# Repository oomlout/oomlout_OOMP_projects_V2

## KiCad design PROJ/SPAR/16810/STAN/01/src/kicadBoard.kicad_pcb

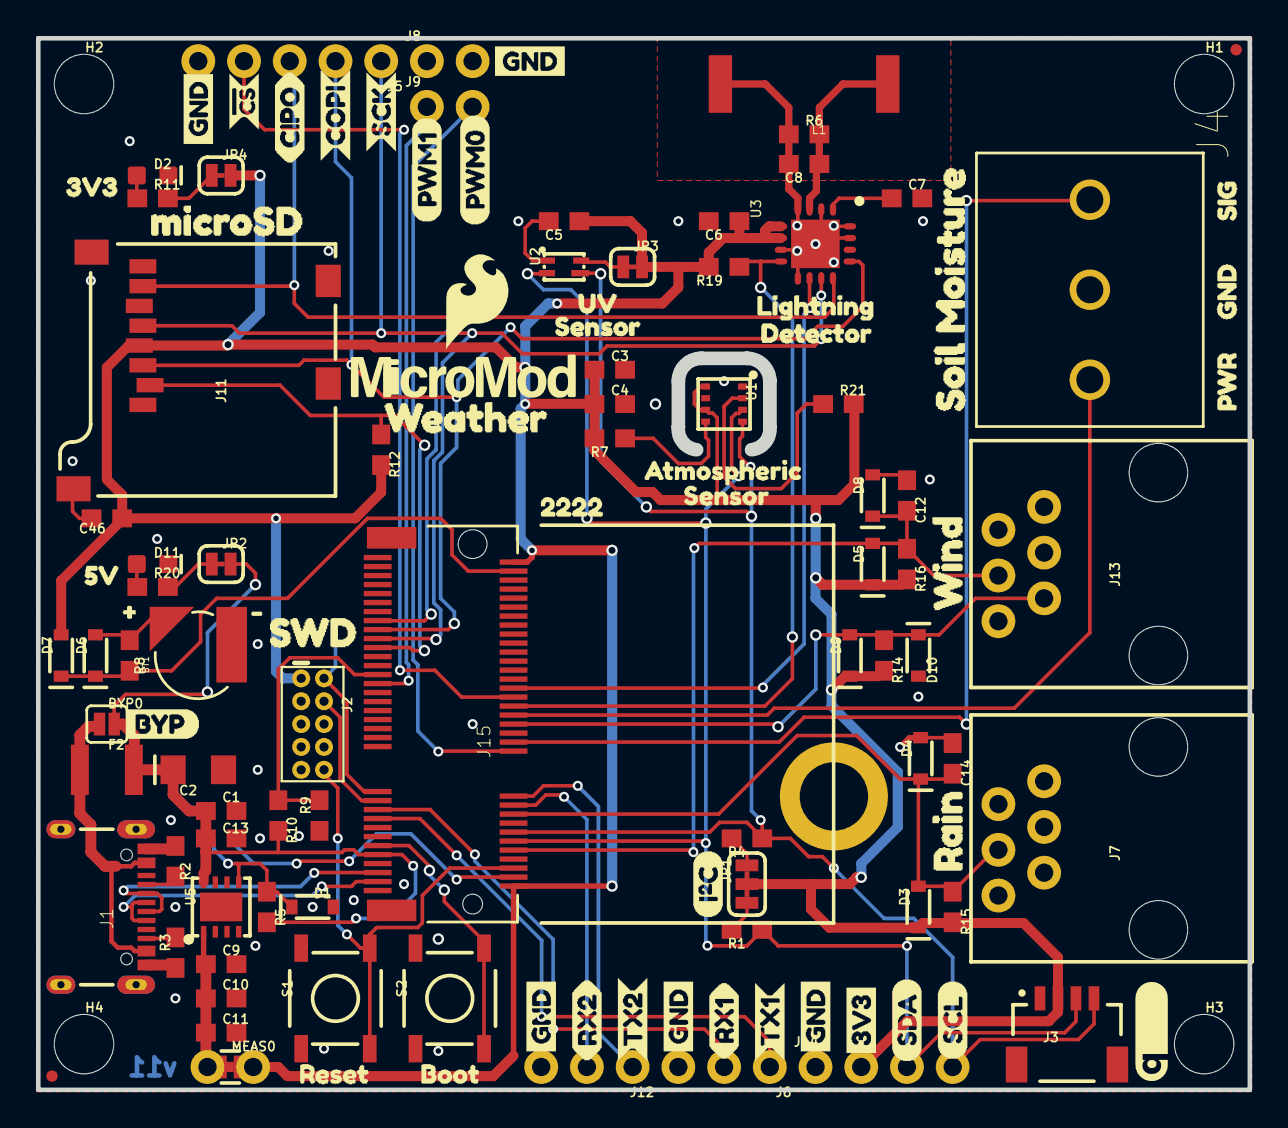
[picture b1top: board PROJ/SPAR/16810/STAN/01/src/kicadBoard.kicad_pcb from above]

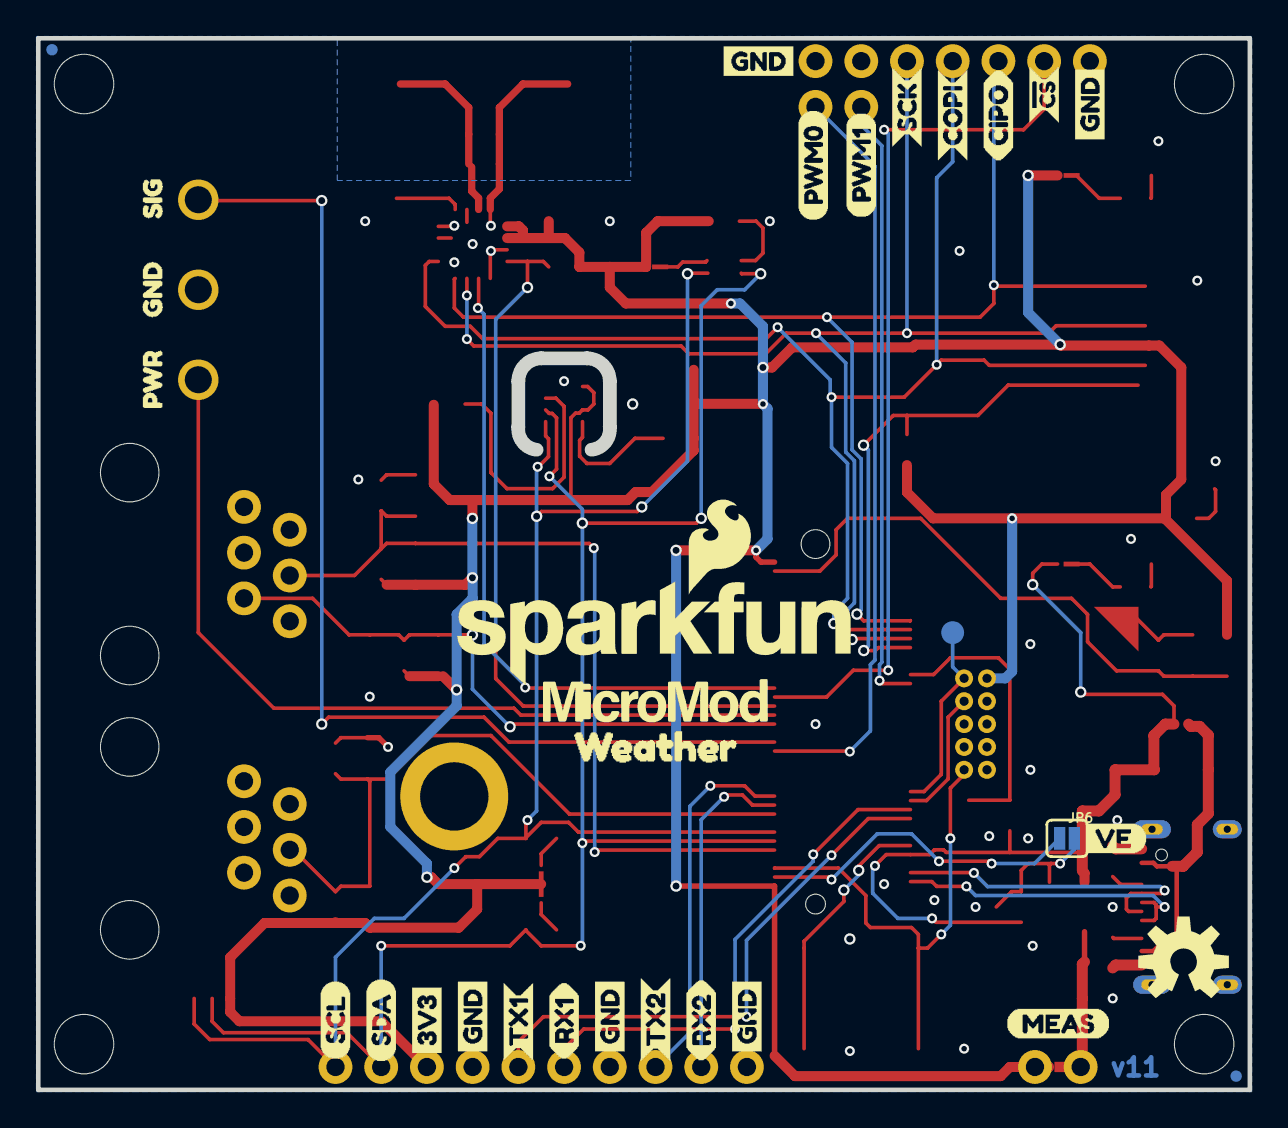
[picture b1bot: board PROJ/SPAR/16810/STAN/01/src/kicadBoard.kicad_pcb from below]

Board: 2 copper layers, 67.3 x 58.4 mm, 157 parts (31 on the bottom side), 49 nets.

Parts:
BT1: ML414H; ML414H_IV01E
BYP0: JUMPER-SMT_2_NO_SILK; SMT-JUMPER_2_NO_SILK
C1, C3, C4, C5, C12, C14, C46: 0.1uF; 0603
C2: 10uF; EIA3216
C6, C10: 1.0uF; 0603
C7, C9: 10uF; 0603
C8: 1nF; 0603
C11, C13: 0.22uF; 0603
D1: 3.3V; SOD-323
D2, D11: RED; LED-0603
D3, D4, D5, D8, D9, D10: 250mA/100V; SOD-323
D6: 3A/10V/280mV; SOD-323
D7: 1A/23V/620mV; SOD-323
F2: 6V/2A; 1210
FD1, FD2, FD3, FD4: FIDUCIALUFIDUCIAL; FIDUCIAL-MICRO
FRAME1: FRAME-LEDGER; CREATIVE_COMMONS
H1, H2, H3, H4: STAND-OFF
H5: STAND-OFF-REFLOW2.5MM_TALL; STAND-OFF-REFLOW-M2.5
J1: USB-C-16P-2LAYER-PADS
J2: JTAG; 2X5-PTH-1.27MM
J3: QWIIC_RIGHT_ANGLE; JST04_1MM_RA
J4: LATCHTERMINAL-5MM-3
J5: 1X05_NO_SILK
J6, J12: 1X03_NO_SILK
J7: RJ11 - RAIN; RJ11-6
J8, J9: 1X02_NO_SILK
J11: microSD; MICRO-SD-SOCKET
J13: RJ11 - WIND; RJ11-6
J14: 1X04_NO_SILK
J15: MICROMOD-2222-C; M.2-CONNECTOR-E
JP1: SMT-JUMPER_3_2-NC_TRACE_SILK
JP2: VIN LED; SMT-JUMPER_2_NC_TRACE_SILK
JP3: UV; SMT-JUMPER_2_NC_TRACE_SILK
JP4: 3V3 LED; SMT-JUMPER_2_NC_TRACE_SILK
JP6: VE; SMT-JUMPER_2_NO_SILK
L1: 100uH; MA5532-AE
LOGO1: SFE_LOGO_NAME_FLAME.2_INCH; SFE_LOGO_NAME_FLAME_.2
LOGO2: QWIIC_LOGO_CONNECTOR; QWIIC_5.5MM
LOGO3: OSHW-LOGOM; OSHW-LOGO-M
MEAS0: COMBO-JUMPER_2_NC_TRACE
R1, R4: 2.2k; 0603
R2, R3: 5.1k; 0603
R5, R12, R19: 100k; 0603
R6, R7, R9, R14, R21: 10k; 0603
R8: 3.3k; 0603
R10: 20k; 0603
R11, R20: 1k; 0603
R15, R16: 43k; 0603
S1: Reset; TACTILE_SWITCH_SMD_5.2MM
S2: BOOT; TACTILE_SWITCH_SMD_5.2MM
TP1: TEST-POINT3X5; PAD.03X.05
U1: BME280; LGA-8-2.5X2.5
U2: VEML6075; VEML6075_A3OP
U3: AS3935; 16LD_MLPQ
U5: AP7361C-33FGEUDFN-8; UDFN-8
U$1: 3V31
U$2: RESET3
U$3: RAIN1
U$4, U$57: GND0
U$5: MEAS
U$6, U$11, U$23, U$32, U$33, U$36, U$42, U$45, U$53, U$54: GND_P
U$7, U$8: COPI0
U$9, U$49: SCK_O
U$10, U$52: !CS_O
U$12, U$24: PWR2
U$13, U$63: SIG1
U$14: BYP0
U$15, U$61: PWM10
U$16, U$58: WEATHER4
U$17, U$30: RX25
U$18: 5V0
U$19: BOOT2
U$20: ATMOSPHERIC0
U$21: VE0
U$22: LIGHTNING8
U$25, U$29: RX10
U$27, U$50: CIPO0
U$28, U$56: TX24
U$31, U$41: TX13
U$34: SENSOR7
U$35: MICROSD0
U$37: I2C
U$38, U$46: 3V3_P
U$39, U$47: SDA_IO
U$40, U$48: SCL_IO
U$43: SWD1
U$44: SFE_LOGO_FLAME_.2
U$55: 22229
U$59, U$60: PWM01
U$62: UV6
U$64: SENSOR1
U$65: SOIL_MOISTURE2
U$66: WIND0
U$67, U$68: MICROMOD_LOGO_.5
U$69: #0
U$70: #1
U$71: DETECTOR2

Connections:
3.3V: C3.1, C4.1, C5.1, C6.1, C46.1, D3.C, D5.C, D7.A, D9.C, J2.1, J3.2, J11.VCC, J14.2, J15.2, J15.74, JP1.2, JP3.2, JP4.2, MEAS0.2, MEAS0.4, R7.2, R12.2, R14.2, R15.2, R16.2, R19.2, R21.2, U1.6, U1.8, U3.5, U3.6
3.3V_EN: J15.4, JP6.1
GND: BT1.-, C1.2, C2.-, C3.2, C4.2, C5.2, C6.2, C7.2, C8.2, C9.2, C10.2, C11.2, C12.1, C13.2, C14.1, C46.2, D1.A, D2.C, D4.A, D8.A, D10.A, D11.C, H5.1, J1.GND, J1.GND2, J2.3, J2.5, J2.9, J3.1, J4.2, J5.5, J6.3, J7.4, J8.1, J8.2, J11.CD1, J11.GND, J11.GND1, J11.GND3, J12.3, J13.4, J13.5, J14.1, J15.1, J15.7, J15.33, J15.36, J15.39, J15.45, J15.75, L1.2, R2.1, R3.1, R6.1, R9.1, S1.1, S1.2, S2.1, S2.2, U1.1, U1.7, U2.1, U3.2, U3.4, U3.7, U3.9, U3.15, U3.16, U3.17, U5.4, U5.EP
HEADER_~CS: J5.4, J15.44
I2C_SCL: J3.4, J14.4, J15.14, R4.1, U1.4, U2.3
I2C_SDA: J3.3, J14.3, J15.12, R1.1, U1.3, U2.2
INP: C8.1, L1.1, R6.2, U3.3
LIGHTNING_INT: J15.46, U3.10
LIGHTNING_~CS: J15.42, R19.1, U3.8
unnamed: C9.1, C10.1, C11.1, MEAS0.1, MEAS0.3, U5.1
unnamed: JP1.3, R4.2
unnamed: JP1.1, R1.2
unnamed: JP4.1, R11.2
unnamed: JP2.1, R20.2
unnamed: D2.A, R11.1
unnamed: JP3.1, U2.4
unnamed: R7.1, U1.5
unnamed: J1.A5, R2.2
unnamed: J1.B5, R3.2
unnamed: BT1.+, D6.A, R8.1
unnamed: C7.1, U3.1
unnamed: D11.A, R20.1
unnamed: R21.1, U1.2
PWM0: J9.2, J15.32
PWM1: J9.1, J15.47
RAIN: C14.2, D3.A, D4.C, J7.3, J15.18, R15.1
RTC_3V: D6.C, D7.C, J15.72, R8.2
RX1: J6.2, J15.19
RX2: J12.2, J15.20
SD_~CS: J11.CS/DAT3, J15.55, R12.1
SOIL_MOIST_PWR: J4.3, J15.40
SOIL_MOIST_SIG: J4.1, J15.34
SPI_CIPO: J5.3, J11.DO/DAT0, J15.61, U3.12
SPI_COPI: J5.2, J11.DI/CMD, J15.59, U3.13
SPI_SCK: J5.1, J11.SCLK, J15.57, U3.11
SWDCK: J2.4, J15.21
SWDIO: J2.2, J15.23, TP1.P$1
TX1: J6.1, J15.17
TX2: J12.1, J15.22
USB_D+: J1.A6, J1.B6, J15.3
USB_D-: J1.A7, J1.B7, J15.5
VIN: BYP0.2, C1.1, C2.+, C13.1, F2.2, J15.9, JP2.2, R5.2, R10.2, U5.8
VIN/3: J15.49, R9.2, R10.1
VREG_EN: D1.C, JP6.2, R5.1, U5.5
V_USB: BYP0.1, F2.1, J1.VBUS1, J1.VBUS2
WDIR: D9.A, D10.C, J13.2, J15.38, R14.1
WSPEED: C12.2, D5.A, D8.C, J13.3, J15.10, R16.1
~BOOT: J15.11, S2.3, S2.4
~RESET: J2.10, J15.6, S1.3, S1.4

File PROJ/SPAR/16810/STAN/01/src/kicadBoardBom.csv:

"Id";"Designator";"Package";"Quantity";"Designation";"Supplier and ref";
1;"U$37";"I2C";1;"";;;
2;"R8";"0603";1;"3.3k";;;
3;"R15,R16";"0603";2;"43k";;;
4;"U$16,U$58";"WEATHER4";2;"";;;
5;"C12,C1,C3,C14,C46,C5,C4";"0603";7;"0.1uF";;;
6;"J12,J6";"1X03_NO_SILK";2;"";;;
7;"JP3";"SMT-JUMPER_2_NC_TRACE_SILK";1;"UV";;;
8;"R20,R11";"0603";2;"1k";;;
9;"MEAS0";"COMBO-JUMPER_2_NC_TRACE";1;"";;;
10;"U2";"VEML6075_A3OP";1;"VEML6075";;;
11;"D5,D9,D8,D3,D4,D10";"SOD-323";6;"250mA/100V";;;
12;"U$39,U$47";"SDA_IO";2;"";;;
13;"D2,D11";"LED-0603";2;"RED";;;
14;"U$64";"SENSOR1";1;"";;;
15;"BYP0";"SMT-JUMPER_2_NO_SILK";1;"JUMPER-SMT_2_NO_SILK";;;
16;"FD2,FD1,FD3,FD4";"FIDUCIAL-MICRO";4;"FIDUCIALUFIDUCIAL";;;
17;"C9,C7";"0603";2;"10uF";;;
18;"J1";"USB-C-16P-2LAYER-PADS";1;"";;;
19;"D1";"SOD-323";1;"3.3V";;;
20;"R14,R21,R7,R9,R6";"0603";5;"10k";;;
21;"H5";"STAND-OFF-REFLOW-M2.5";1;"STAND-OFF-REFLOW2.5MM_TALL";;;
22;"D7";"SOD-323";1;"1A/23V/620mV";;;
23;"J11";"MICRO-SD-SOCKET";1;"microSD";;;
24;"R5,R12,R19";"0603";3;"100k";;;
25;"L1";"MA5532-AE";1;"100uH";;;
26;"BT1";"ML414H_IV01E";1;"ML414H";;;
27;"FRAME1";"CREATIVE_COMMONS";1;"FRAME-LEDGER";;;
28;"J4";"LATCHTERMINAL-5MM-3";1;"";;;
29;"U$19";"BOOT2";1;"";;;
30;"U$70";"#1";1;"";;;
31;"R4,R1";"0603";2;"2.2k";;;
32;"U$69";"#0";1;"";;;
33;"U$18";"5V0";1;"";;;
34;"J2";"2X5-PTH-1.27MM";1;"JTAG";;;
35;"U$43";"SWD1";1;"";;;
36;"U$29,U$25";"RX10";2;"";;;
37;"LOGO2";"QWIIC_5.5MM";1;"QWIIC_LOGO_CONNECTOR";;;
38;"U$27,U$50";"CIPO0";2;"";;;
39;"U$67,U$68";"MICROMOD_LOGO_.5";2;"";;;
40;"H3,H1,H2,H4";"STAND-OFF";4;"STAND-OFF";;;
41;"J14";"1X04_NO_SILK";1;"";;;
42;"C13,C11";"0603";2;"0.22uF";;;
43;"U5";"UDFN-8";1;"AP7361C-33FGEUDFN-8";;;
44;"J13";"RJ11-6";1;"RJ11 - WIND";;;
45;"U$71";"DETECTOR2";1;"";;;
46;"U1";"LGA-8-2.5X2.5";1;"BME280";;;
47;"U$14";"BYP0";1;"";;;
48;"R3,R2";"0603";2;"5.1k";;;
49;"U$66";"WIND0";1;"";;;
50;"U$10,U$52";"!CS_O";2;"";;;
51;"U$44";"SFE_LOGO_FLAME_.2";1;"";;;
52;"C6,C10";"0603";2;"1.0uF";;;
53;"U3";"16LD_MLPQ";1;"AS3935";;;
54;"U$17,U$30";"RX25";2;"";;;
55;"U$60,U$59";"PWM01";2;"";;;
56;"J15";"M.2-CONNECTOR-E";1;"MICROMOD-2222-C";;;
57;"U$13,U$63";"SIG1";2;"";;;
58;"C8";"0603";1;"1nF";;;
59;"JP1";"SMT-JUMPER_3_2-NC_TRACE_SILK";1;"";;;
60;"U$20";"ATMOSPHERIC0";1;"";;;
61;"U$65";"SOIL_MOISTURE2";1;"";;;
62;"U$31,U$41";"TX13";2;"";;;
63;"U$62";"UV6";1;"";;;
64;"U$6,U$36,U$54,U$33,U$32,U$23,U$42,U$11,U$53,U$45";"GND_P";10;"";;;
65;"U$40,U$48";"SCL_IO";2;"";;;
66;"JP2";"SMT-JUMPER_2_NC_TRACE_SILK";1;"VIN LED";;;
67;"U$4,U$57";"GND0";2;"";;;
68;"F2";"1210";1;"6V/2A";;;
69;"J9,J8";"1X02_NO_SILK";2;"";;;
70;"U$55";"22229";1;"";;;
71;"S1";"TACTILE_SWITCH_SMD_5.2MM";1;"Reset";;;
72;"U$1";"3V31";1;"";;;
73;"U$2";"RESET3";1;"";;;
74;"U$34";"SENSOR7";1;"";;;
75;"U$56,U$28";"TX24";2;"";;;
76;"J7";"RJ11-6";1;"RJ11 - RAIN";;;
77;"D6";"SOD-323";1;"3A/10V/280mV";;;
78;"U$38,U$46";"3V3_P";2;"";;;
79;"J3";"JST04_1MM_RA";1;"QWIIC_RIGHT_ANGLE";;;
80;"U$61,U$15";"PWM10";2;"";;;
81;"R10";"0603";1;"20k";;;
82;"J5";"1X05_NO_SILK";1;"";;;
83;"U$35";"MICROSD0";1;"";;;
84;"C2";"EIA3216";1;"10uF";;;
85;"U$12,U$24";"PWR2";2;"";;;
86;"U$3";"RAIN1";1;"";;;
87;"U$7,U$8";"COPI0";2;"";;;
88;"U$9,U$49";"SCK_O";2;"";;;
89;"S2";"TACTILE_SWITCH_SMD_5.2MM";1;"BOOT";;;
90;"U$22";"LIGHTNING8";1;"";;;
91;"JP4";"SMT-JUMPER_2_NC_TRACE_SILK";1;"3V3 LED";;;
92;"TP1";"PAD.03X.05";1;"TEST-POINT3X5";;;
93;"JP6";"SMT-JUMPER_2_NO_SILK";1;"VE";;;
94;"U$21";"VE0";1;"";;;
95;"LOGO1";"SFE_LOGO_NAME_FLAME_.2";1;"SFE_LOGO_NAME_FLAME.2_INCH";;;
96;"LOGO3";"OSHW-LOGO-M";1;"OSHW-LOGOM";;;
97;"U$5";"MEAS";1;"";;;

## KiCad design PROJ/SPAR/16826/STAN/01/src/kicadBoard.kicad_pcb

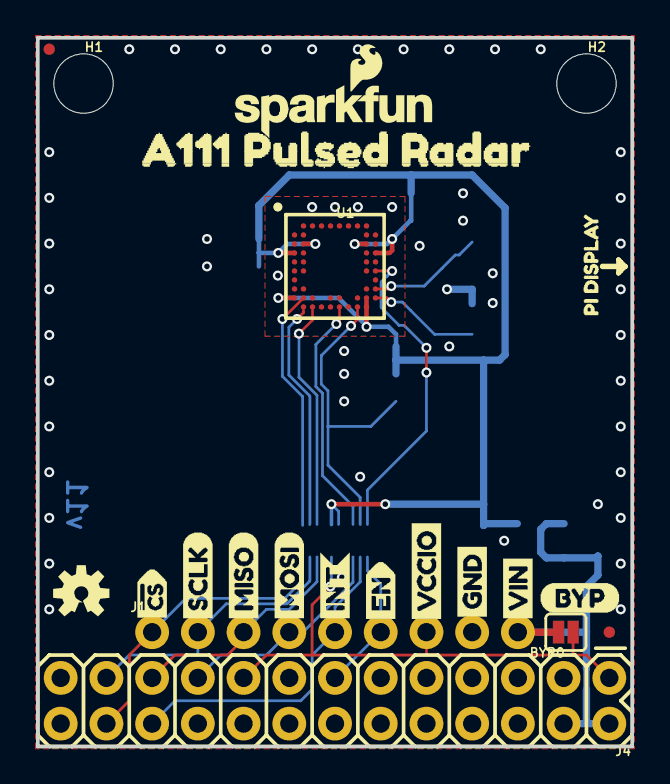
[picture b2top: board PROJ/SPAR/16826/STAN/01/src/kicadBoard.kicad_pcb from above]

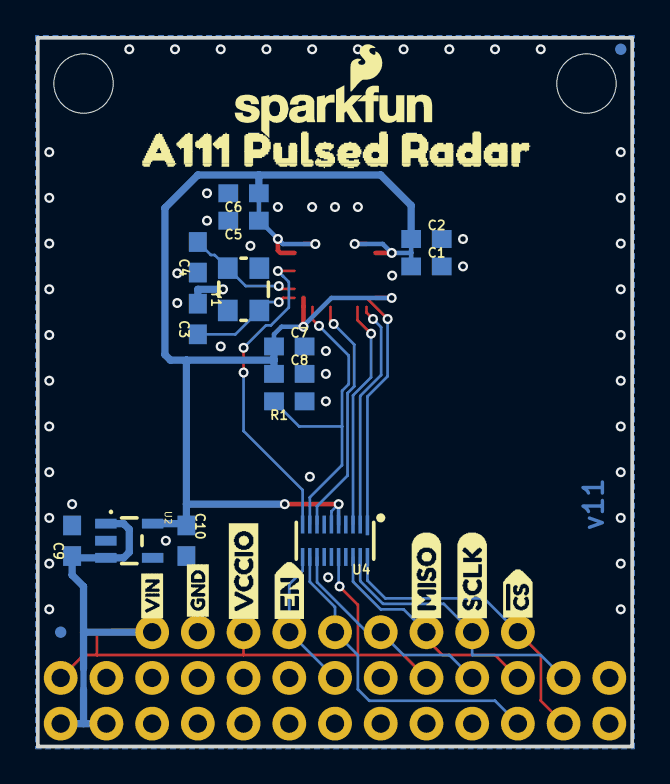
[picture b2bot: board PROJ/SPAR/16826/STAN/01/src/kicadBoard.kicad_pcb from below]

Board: 2 copper layers, 33.0 x 39.4 mm, 48 parts (25 on the bottom side), 18 nets.

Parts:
BYP0: JUMPER-SMT_2_NO_SILK; SMT-JUMPER_2_NO_SILK
C1, C5, C7: 0.1uF; 0603
C2, C6, C8, C9, C10: 1.0uF; 0603
C3, C4: 10pF; 0603
FD1, FD2, FD3, FD4: FIDUCIALUFIDUCIAL; FIDUCIAL-MICRO
FRAME1: FRAME-LETTER; CREATIVE_COMMONS
H1, H2: STAND-OFF
J1: 1X09_NO_SILK
J4: RASPBERRYPI-26-PIN-GPIO; 2X13
LOGO1, LOGO3: SFE_LOGO_NAME_FLAME.1_INCH; SFE_LOGO_NAME_FLAME_.1
LOGO2: OSHW-LOGOS; OSHW-LOGO-S
R1: 100k; 0603
U1: A111
U2: AP2127K-1.8V; SOT23-5
U4: TXB0108DQSR; UFDFN-20
U$1, U$9: A111_PULSED_RADAR9
U$2, U$10: SCLK3
U$3, U$11: MISO4
U$4: MOSI5
U$5: INT8
U$6, U$18: EN9
U$7: GND0
U$8: BYP
U$12: PI_DISPLAY9
U$13, U$17: #CS9
U$16: VIN0
U$19, U$20: VCCIO1
U$21: GND6
U$22: VIN5
Y1: 26MHz; CRYSTAL-SMD-3.2X2.5MM

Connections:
1.8V: C1.1, C2.1, C5.1, C6.1, C7.1, C8.1, C10.1, U1.C2, U1.C9, U1.D1, U1.D10, U1.J1, U1.J9, U1.K9, U2.5, U4.5, U4.6
ENABLE: U1.F10, U4.10
ENABLE_RPI: J1.6, J4.13, U4.11
GND: C1.2, C2.2, C3.2, C4.1, C5.2, C6.2, C7.2, C8.2, C9.2, C10.2, J1.8, J4.6, J4.9, J4.14, J4.20, J4.25, R1.1, U1.A3, U1.A4, U1.A5, U1.A6, U1.A7, U1.A8, U1.A9, U1.B2, U1.B9, U1.B10, U1.C1, U1.C10, U1.D2, U1.D9, U1.E1, U1.E2, U1.E9, U1.E10, U1.F1, U1.F2, U1.F9, U1.G1, U1.G10, U1.H1, U1.H2, U1.H9, U1.J3, U1.J5, U1.J6, U1.J8, U1.K4, U1.K5, U1.K7, U2.2, U4.15, Y1.2, Y1.4
INTERRUPT: R1.2, U1.K8, U4.9
INTERRUPT_RPI: J1.5, J4.22, U4.12
MISO: U1.K3, U4.3
MISO_RPI: J1.3, J4.21, U4.18
MOSI: U1.K6, U4.8
MOSI_RPI: J1.4, J4.19, U4.13
unnamed: C3.1, U1.J10, Y1.1
unnamed: C4.2, U1.H10, Y1.3
SCLK: U1.K2, U4.2
SCLK_RPI: J1.2, J4.23, U4.19
VCCIO: BYP0.1, J1.7, J4.1, J4.17, U4.16
VIN: BYP0.2, C9.1, J1.9, J4.2, J4.4, U2.1, U2.3
~CS: U1.J2, U4.1
~CS_RPI: J1.1, J4.24, U4.20

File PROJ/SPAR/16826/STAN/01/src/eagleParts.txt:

Partlist

Exported from boardEagle.brd at 20/08/2022 05:57

EAGLE Version 9.6.2 Copyright (c) 1988-2020 Autodesk, Inc.

Assembly variant: 

Part     Value                   Package               Library             Position (inch)       Orientation

BYP      JUMPER-SMT_2_NO_SILK    SMT-JUMPER_2_NO_SILK  SparkFun-Jumpers    (1.155 0.25)          R180
C1       0.1uF                   0603                  SparkFun-Capacitors (0.45 1.05)           MR0
C2       1.0uF                   0603                  SparkFun-Capacitors (0.45 1.11)           MR0
C3       10pF                    0603                  SparkFun-Capacitors (0.95 0.935)          MR90
C4       10pF                    0603                  SparkFun-Capacitors (0.95 1.07)           MR90
C5       0.1uF                   0603                  SparkFun-Capacitors (0.85 1.15)           MR180
C6       1.0uF                   0603                  SparkFun-Capacitors (0.85 1.21)           MR180
C7       0.1uF                   0603                  SparkFun-Capacitors (0.75 0.875)          MR0
C8       1.0uF                   0603                  SparkFun-Capacitors (0.75 0.815)          MR0
C9       1.0uF                   0603                  SparkFun-Capacitors (1.225 0.45)          MR90
C10      1.0uF                   0603                  SparkFun-Capacitors (0.975 0.45)          MR270
FD1      FIDUCIALUFIDUCIAL       FIDUCIAL-MICRO        SparkFun-Aesthetics (1.25 0.25)           R0
FD2      FIDUCIALUFIDUCIAL       FIDUCIAL-MICRO        SparkFun-Aesthetics (0.025 1.525)         R0
FD3      FIDUCIALUFIDUCIAL       FIDUCIAL-MICRO        SparkFun-Aesthetics (0.025 1.525)         MR0
FD4      FIDUCIALUFIDUCIAL       FIDUCIAL-MICRO        SparkFun-Aesthetics (1.25 0.25)           MR0
J1                               1X09_NO_SILK          SparkFun-Connectors (0.25 0.25)           R0
J4       RASPBERRYPI-26-PIN-GPIO 2X13                  SparkFun-Connectors (1.25 0.15)           R180
R1       100k                    0603                  SparkFun-Resistors  (0.75 0.755)          MR180
U1       A111                    A111                  SparkFun-Sensors    (0.65 1.05)           R0
U2       AP2127K-1.8V            SOT23-5               SparkFun-IC-Power   (1.1 0.45)            MR270
U4       TXB0108DQSR             UFDFN-20              SparkFun-IC-Comms   (0.65 0.45)           MR180
Y1       26MHz                   CRYSTAL-SMD-3.2X2.5MM SparkFun-Clocks     (0.85 1)              MR90

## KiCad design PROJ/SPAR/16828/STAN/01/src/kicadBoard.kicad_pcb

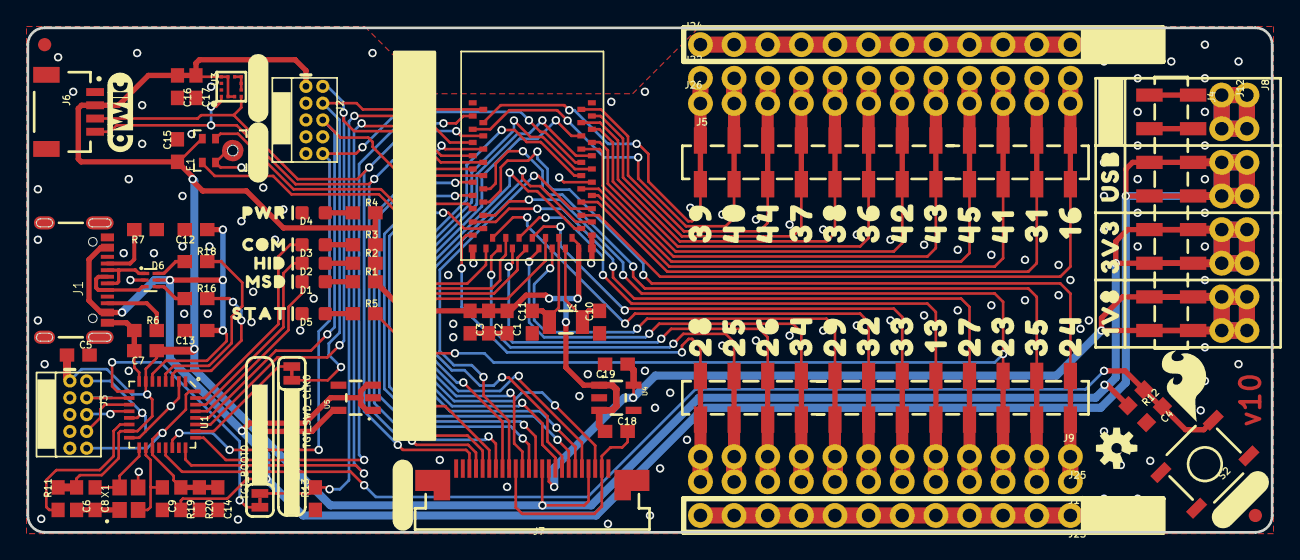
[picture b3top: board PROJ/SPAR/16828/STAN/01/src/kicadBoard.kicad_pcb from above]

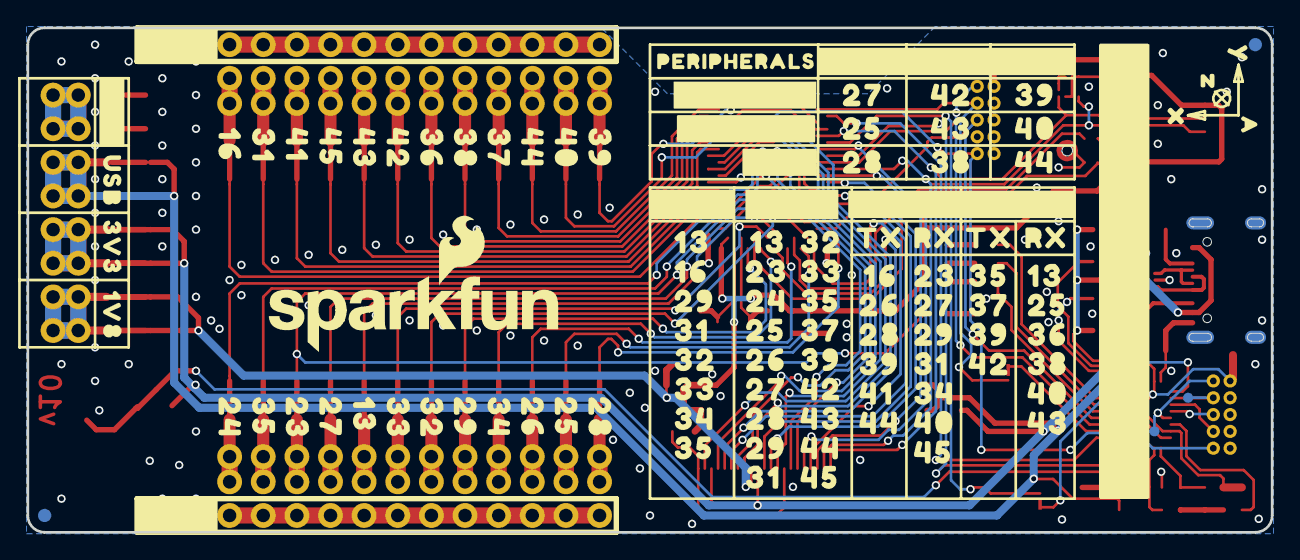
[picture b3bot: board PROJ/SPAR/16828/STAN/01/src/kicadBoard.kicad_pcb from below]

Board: 2 copper layers, 94.0 x 38.1 mm, 229 parts (113 on the bottom side), 82 nets.

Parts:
C1, C17: 10uF; 0603
C2, C12, C15, C18, C19: 1.0uF; 0603
C3, C4, C6, C7, C13, C14, C16: 0.1uF; 0603
C5: 2.2uF; 0603
C8, C9: 12pF; 0603
C10, C11: 15pF; 0603
D1, D5: BLUE; LED-0603
D2: GREEN; LED-0603
D3: Yellow; LED-0603
D4: RED; LED-0603
D6: PRTR5V0U2F; SOT886
E1: SPH0641LM4H-1; SPH0641LM4H-1_MICROPHONE
FD1, FD2, FD3, FD4: FIDUCIAL1X2; FIDUCIAL-1X2
FRAME1: FRAME-LEDGER; CREATIVE_COMMONS
J1: USB; USB-C-16P
J2: CORTEX_JTAG_DEBUG_MINIMUM_PTH; 2X5-PTH-1.27MM
J3: CORTEX_JTAG_DEBUG_PTH; 2X5-PTH-1.27MM
J4: SMD; 1X08_SMD_COMBINED
J5, J9: 1X12_SMD_COMBINED
J6: QWIIC_RIGHT_ANGLE; JST04_1MM_RA
J7: CAMERA-HIMAXBOTTOM-CONTACT; FPC-24-AMPHENOL-SFV24R-1STE1HLF
J8, J12: PTH; 1X08_NO_SILK
J14, J22, J23, J24, J25, J26: PTH; 1X12_NO_SILK
LOGO1: OSHW-LOGOS; OSHW-LOGO-S
LOGO2: SFE_LOGO_NAME_FLAME.2_INCH; SFE_LOGO_NAME_FLAME_.2
R1, R2, R3, R4, R5: 330; 0603
R6, R7: 5.1k; 0603
R11, R12, R13, R20: 10k; 0603
R16, R18: 33; 0603
R19: 5.62k; 0603
S2: TGT_RST; TACTILE_SWITCH_SMD_5.2MM
TGT_BOOT0: JUMPER-SMT_2_NC_TRACE_SILK; SMT-JUMPER_2_NC_TRACE_SILK
TGT_SWD_CLK0: JUMPER-SMT_2_NC_TRACE_SILK; SMT-JUMPER_2_NC_TRACE_SILK
TP1: INTFC_SWDIO; PAD.03X.03
TP2: INTFC_SWDCLK; PAD.03X.03
U1: DAPLINK_KL26Z128VFM4; QFN-32-NOPAD
U2: ARTEMIS_MODULESMD; ARTEMIS_FP
U3: LIS2DH12; LGA-12-LISDH12
U4: AP2127K-1.8V; SOT23-5
U5: 3.3V; SOT23-5
U$1, U$2: #GND#10
U$3, U$132: 15_#GND#
U$4, U$129: 16_1V8
U$5, U$130: 17_3V3
U$6, U$131: 18_USB
U$7, U$64, U$98, U$147: 33_16
U$8, U$73, U$97, U$149, U$154: 41_31
U$9, U$68, U$96: 51_41
U$10, U$55, U$76, U$163: 55_45
U$11, U$54, U$86, U$91, U$161: 53_43
U$12, U$53, U$80, U$90, U$160: 52_42
U$13, U$52, U$83: 46_36
U$14, U$51, U$84, U$92: 48_38
U$15, U$50, U$78, U$158: 47_37
U$16, U$49, U$69, U$95, U$162: 54_44
U$17, U$48, U$75, U$85, U$94: 50_40
U$18, U$47, U$67, U$79, U$93, U$159: 49_39
U$19, U$58, U$110: 35_24
U$20, U$77, U$109, U$153, U$157: 45_35
U$21, U$57, U$70, U$108: 34_23
U$22, U$61, U$71, U$87, U$107: 38_27
U$23, U$56, U$81, U$106, U$146: 32_13
U$24, U$105, U$151, U$156: 43_33
U$25, U$104, U$150, U$155: 42_32
U$26, U$63, U$72, U$103, U$148: 40_29
U$27, U$74, U$102, U$152: 44_34
U$28, U$60, U$65, U$101: 37_26
U$29, U$59, U$82, U$88, U$100: 36_25
U$30, U$62, U$66, U$89, U$99: 39_28
U$31: 19_#IOM2#
U$32: QWIIC_6MM
U$33: 20_#IOM3#
U$34: 21_#IOM4#
U$35: #TGT#3
U$36: #ARTEMIS_DEV_KIT#0
U$37: #SCL#SCK#23
U$38: 30_#PWM#
U$39: 29_#ADC#
U$40: 25_#UART0#
U$41: 26_#UART1#
U$42, U$43: 27_TX
U$44, U$46: 28_RX
U$45: SFE_LOGO_FLAME_.2
U$111: #SDA#SDI#24
U$112: #SDO#25
U$113: 14_A
U$114: 15_X
U$115: 16_Y
U$116: 17_Z
U$117: 7_COM
U$118: 8_HID
U$119: 9_MSD
U$120: 10_STAT
U$121: 6_PWR
U$122: #ARTEMIS_DEV_KIT#1
U$123: #INTFC#2
U$124: #TGT_BOOT#4
U$125: #TGT_SWD_CLK#5
U$126: #CAM#13
U$137: #MIC#11
U$138: #ACC#12
U$140, U$141: 14_#GND#
U$142: ##RST##18
U$145: 19_PERIPHERALS
X1: 16MHz; CRYSTAL-SMD-2X2.5MM
Y1: 32.768kHz; CRYSTAL-SMD-3.2X1.5MM

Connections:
1.8V: C19.1, J4.7, J4.7@2, J4.8, J4.8@2, J7.10, J8.7, J8.8, J12.7, J12.8, U4.5
3.3V: C1.1, C2.1, C3.1, C5.1, C6.1, C7.1, C15.1, C16.1, C17.1, C18.1, E1.5, J2.1, J3.1, J4.5, J4.5@2, J4.6, J4.6@2, J6.2, J7.4, J7.11, J8.5, J8.6, J12.5, J12.6, R1.2, R2.2, R3.2, R4.2, R11.2, R12.2, U1.7, U1.15, U2.VDD@36, U2.VDD@37, U3.2, U3.3, U3.9, U3.10, U4.1, U4.3, U5.5
CAMERA_D0: J7.14, U2.D0
CAMERA_D1: J7.3, U2.D1
CAMERA_D2: J7.9, U2.D2
CAMERA_D3: J7.5, U2.D3
CAMERA_D4: J7.12, U2.~D4
CAMERA_D5: J7.20, U2.~D5
CAMERA_D6: J7.19, U2.~D6
CAMERA_D7: J7.13, U2.D7
CAMERA_HSYNC: J7.16, U2.D17
CAMERA_INT: J7.18, U2.D10
CAMERA_MCLK: J7.8, U2.~D18
CAMERA_PCLK: J7.17, U2.~D19
CAMERA_TRIG: J7.7, U2.D14
CAMERA_VSYNC: J7.6, U2.D15
D13: J9.5, J9.5@2, J14.5, J25.5, U2.~AD13
D16: J5.12, J5.12@2, J22.12, J26.12, U2.AD16
D23_LED: J9.3, J9.3@2, J14.3, J25.3, R5.2, U2.~D23
D24: J9.1, J9.1@2, J14.1, J25.1, U2.~D24
D25: J9.11, J9.11@2, J14.11, J25.11, U2.~D25
D26: J9.10, J9.10@2, J14.10, J25.10, U2.~D26
D27: J9.4, J9.4@2, J14.4, J25.4, U2.~D27
D28: J9.12, J9.12@2, J14.12, J25.12, U2.~D28
D29: J9.8, J9.8@2, J14.8, J25.8, U2.~AD29
D31: J5.11, J5.11@2, J22.11, J26.11, U2.~AD31
D32: J9.7, J9.7@2, J14.7, J25.7, U2.~AD32
D33: J9.6, J9.6@2, J14.6, J25.6, U2.~AD33/SWO
D34: J9.9, J9.9@2, J14.9, J25.9, U2.AD34
D35: J9.2, J9.2@2, J14.2, J25.2, U2.~AD35
D36: J5.6, J5.6@2, J22.6, J26.6, U2.D36
D37: J5.4, J5.4@2, J22.4, J26.4, U2.~D37
D38: J5.5, J5.5@2, J22.5, J26.5, U2.D38
D39: J5.1, J5.1@2, J22.1, J26.1, U2.~D39
D40: J5.2, J5.2@2, J22.2, J26.2, U2.D40
D41: J5.10, J5.10@2, J22.10, J26.10, U2.D41
D42: J5.7, J5.7@2, J22.7, J26.7, U2.~D42
D43: J5.8, J5.8@2, J22.8, J26.8, U2.~D43
D44: J5.3, J5.3@2, J22.3, J26.3, U2.~D44
D45: J5.9, J5.9@2, J22.9, J26.9, U2.~D45
GND: C1.2, C2.2, C3.2, C4.2, C5.2, C6.2, C7.2, C8.2, C9.2, C10.1, C11.1, C12.2, C13.2, C14.2, C15.2, C16.2, C17.2, C18.2, C19.2, D4.C, D5.C, D6.2, E1.2, E1.3, E1.6, E1.7, E1.8, J1.GND, J1.GND2, J2.3, J2.5, J2.9, J3.3, J3.5, J3.9, J4.1, J4.1@2, J4.2, J4.2@2, J6.1, J7.2, J7.15, J8.1, J8.2, J12.1, J12.2, J23.1, J23.2, J23.3, J23.4, J23.5, J23.6, J23.7, J23.8, J23.9, J23.10, J23.11, J23.12, J24.1, J24.2, J24.3, J24.4, J24.5, J24.6, J24.7, J24.8, J24.9, J24.10, J24.11, J24.12, R6.1, R7.1, R13.1, R20.2, S2.1, U1.2, U1.8, U1.16, U2.GND@1, U2.GND@22, U2.GND@38, U2.GND@39, U2.GND@47, U2.GND@59, U3.5, U3.6, U3.7, U3.8, U4.2, U5.2, X1.P2, X1.P4
INTFC_NC5: J3.8, U1.11
INTFC_NC6: J3.6, U1.12
INTFC_SWDCLK: J3.4, TP2.P$1, U1.10
INTFC_SWDIO: J3.2, TP1.P$1, U1.13
LED_HID: D2.C, U1.30
LED_MSD: D1.C, U1.29
LED_UART: D3.C, U1.31
unnamed: D1.A, R1.1
unnamed: D2.A, R2.1
unnamed: D3.A, R3.1
unnamed: J1.B5, R6.2
unnamed: J1.A5, R7.2
unnamed: D5.A, R5.1
unnamed: D4.A, R4.1
unnamed: D6.4, R16.1
unnamed: D6.6, R18.1
unnamed: R11.1, U1.14
unnamed: TGT_SWD_CLK0.1, U1.26
unnamed: C8.1, U1.17, X1.P1
unnamed: C10.2, U2.XI, Y1.P$2
unnamed: C11.2, U2.XO, Y1.P$1
unnamed: C9.1, U1.18, X1.P3
unnamed: TGT_BOOT0.1, U1.9
PDM_CLK: E1.4, U2.~AD12
PDM_DATA: E1.1, U2.~AD11
SCL: J6.4, J7.21, U2.D8, U3.1
SDA: J6.3, J7.22, U2.D9, U3.4
TGT_BOOT: R13.2, TGT_BOOT0.2, U2.BOOT
TGT_RX: U1.25, U2.RXI-0
TGT_SWCLK: J2.4, TGT_SWD_CLK0.2, U2.SWDCK
TGT_SWDIO: J2.2, U1.27, U2.SWDIO
TGT_SWO: J2.6, U1.28, U2.~D22
TGT_TX: U1.24, U2.TXO-0
USB_D+_P: R16.2, U1.3
USB_D+_R: D6.3, J1.A6, J1.B6
USB_D-_P: R18.2, U1.4
USB_D-_R: D6.1, J1.A7, J1.B7
V_USB: C12.1, C13.1, D6.5, J1.VBUS1, J1.VBUS2, J4.3, J4.3@2, J4.4, J4.4@2, J8.3, J8.4, J12.3, J12.4, R19.2, U1.6, U5.1, U5.3
~INTFC_RST: C14.1, J3.10, R19.1, R20.1, U1.19, U1.32
~RST_BTN: C4.1, R12.1, S2.3, U1.21
~TGT_RST: J2.10, U1.22, U2.~RST

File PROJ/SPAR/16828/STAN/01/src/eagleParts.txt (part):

Partlist

Exported from boardEagle.brd at 20/08/2022 06:00

EAGLE Version 9.6.2 Copyright (c) 1988-2020 Autodesk, Inc.

Assembly variant: 

Part        Value                         Package                         Library                     Position (mil)        Orientation

C1          10uF                          0603                            SparkFun-Capacitors         (1425 625)            R270
C2          1.0uF                         0603                            SparkFun-Capacitors         (1370 625)            R270
C3          0.1uF                         0603                            SparkFun-Capacitors         (1315 625)            R270
C4          0.1uF                         0603                            SparkFun-Capacitors         (3350 350)            R225
C5          2.2uF                         0603                            SparkFun-Capacitors         (150 527)             R0
C6          0.1uF                         0603                            SparkFun-Capacitors         (145 100)             R270
C7          0.1uF                         0603                            SparkFun-Capacitors         (350 540)             R180
C8          12pF                          0603                            SparkFun-Capacitors         (200 100)             R270
C9          12pF                          0603                            SparkFun-Capacitors         (400 100)             R270
C10         15pF                          0603                            SparkFun-Capacitors         (1700 625)            R90
C11         15pF                          0603                            SparkFun-Capacitors         (1500 625)            R90
C12         1.0uF                         0603                            SparkFun-Capacitors         (500 900)             R180
C13         0.1uF                         0603                            SparkFun-Capacitors         (500 600)             R180
C14         0.1uF                         0603                            SparkFun-Capacitors         (565 100)             R270
C15         1.0uF                         0603                            SparkFun-Capacitors         (445 1135)            R90
C16         0.1uF                         0603                            SparkFun-Capacitors         (445 1325)            R270
C17         10uF                          0603                            SparkFun-Capacitors         (500 1325)            R270
C18         1.0uF                         0603                            SparkFun-Capacitors         (1750 300)            R0
C19         1.0uF                         0603                            SparkFun-Capacitors         (1750 500)            R180
D1          BLUE                          LED-0603                        SparkFun-LED                (850 745)             R180
D2          GREEN                         LED-0603                        SparkFun-LED                (850 800)             R180
D3          Yellow                        LED-0603                        SparkFun-LED                (850 855)             R180
D4          RED                           LED-0603                        SparkFun-LED                (850 950)             R180
D5          BLUE                          LED-0603                        SparkFun-LED                (850 650)             R180
D6          PRTR5V0U2F                    SOT886                          SparkFun-IC-Power           (365 750)             R0
E1          SPH0641LM4H-1                 SPH0641LM4H-1_MICROPHONE        SparkFun-Sensors            (570 1135)            R90
FD1         FIDUCIAL1X2                   FIDUCIAL-1X2                    SparkFun-Aesthetics         (50 1450)             R0
FD2         FIDUCIAL1X2                   FIDUCIAL-1X2                    SparkFun-Aesthetics         (50 1450)             MR0
FD3         FIDUCIAL1X2                   FIDUCIAL-1X2                    SparkFun-Aesthetics         (3650 50)             R0
FD4         FIDUCIAL1X2                   FIDUCIAL-1X2                    SparkFun-Aesthetics         (3650 50)             MR0
J1          USB                           USB-C-16P                       SparkFun-Connectors         (250 750)             R270
J2          CORTEX_JTAG_DEBUG_MINIMUM_PTH 2X5-PTH-1.27MM                  SparkFun-Connectors         (852 1226)            R270
J3          CORTEX_JTAG_DEBUG_PTH         2X5-PTH-1.27MM                  SparkFun-Connectors         (150 350)             R270
J4          SMD                           1X08_SMD_COMBINED               SparkFun-Connectors         (3400 1300)           R270
J5                                        1X12_SMD_COMBINED               SparkFun-Connectors         (2000 1100)           R0
J6          QWIIC_RIGHT_ANGLE             JST04_1MM_RA                    SparkFun-Connectors         (200 1250)            R270
J7          CAMERA-HIMAXBOTTOM-CONTACT    FPC-24-AMPHENOL-SFV24R-1STE1HLF SparkFun-Connectors         (1500 95)             R0
J8          PTH                           1X08_NO_SILK                    SparkFun-Connectors         (3625 1300)           R270
J9                                        1X12_SMD_COMBINED               SparkFun-Connectors         (3100 400)            R180
J12         PTH                           1X08_NO_SILK                    SparkFun-Connectors         (3550 1300)           R270
J14         PTH                           1X12_NO_SILK                    SparkFun-Connectors         (3100 150)            R180
J22         PTH                           1X12_NO_SILK                    SparkFun-Connectors         (2000 1350)           R0
J23         PTH                           1X12_NO_SILK                    SparkFun-Connectors         (3100 50)             R180
J24         PTH                           1X12_NO_SILK                    SparkFun-Connectors         (2000 1450)           R0
J25         PTH                           1X12_NO_SILK                    SparkFun-Connectors         (3100 225)            R180
J26         PTH                           1X12_NO_SILK                    SparkFun-Connectors         (2000 1275)           R0
R1          330                           0603                            SparkFun-Resistors          (1000 745)            R0
R2          330                           0603                            SparkFun-Resistors          (1000 800)            R0
R3          330                           0603                            SparkFun-Resistors          (1000 855)            R0
R4          330                           0603                            SparkFun-Resistors          (1000 950)            R0
R5          330                           0603                            SparkFun-Resistors          (1000 650)            R0
R6          5.1k                          0603                            SparkFun-Resistors          (350 600)             R0
R7          5.1k                          0603                            SparkFun-Resistors          (350 900)             R180
R11         10k                           0603                            SparkFun-Resistors          (90 100)              R90
R12         10k                           0603                            SparkFun-Resistors          (3295 400)            R225
R13         10k                           0603                            SparkFun-Resistors          (855 100)             R90
R16         33                            0603                            SparkFun-Resistors          (500 695)             R0
R18         33                            0603                            SparkFun-Resistors          (500 805)             R0
R19         5.62k                         0603                            SparkFun-Resistors          (455 100)             R270
R20         10k                           0603                            SparkFun-Resistors          (510 100)             R270
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

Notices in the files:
parts and their libraries:
RELEASED UNDER THE CREATIVE COMMONS ATTRIBUTION SHARE-ALIKE 4.0 LICENSE
HTTPS://CREATIVECOMMONS.ORG/LICENSES/BY-SA/4.0
